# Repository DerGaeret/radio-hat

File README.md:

# Retro-Radio

Holzgehäuse mit Frontplatte und Lautsprecherabdeckungen eines DDR-Radios. Innen ein Raspberry Pi 4B mit dem **Raspberry Pi DigiAMP+** als Verstärker, sechs Tasten, drei Drehgebern (nur Drehen), dem Original-A/E-Schalter mit softem Ausschalten und, als Option, einer LED-Skala mit Senderzeiger. Alles zum Bestellen steht in **`EINKAUF.md`**.

Bis zum 17.11.2026 war hier eine eigene Verstärkerplatine (Radio HAT, TAS5805M) entworfen. Sie wird nicht gebaut; der DigiAMP+ macht dasselbe. Der letzte Stand liegt in der Git-Geschichte (Commit `c25365f`), zurückholen mit `git checkout c25365f -- KiCad JLCPCB PRUEFBERICHT.md`.

| Datei | Wofür |
|---|---|
| `Pi/asound.conf` | ALSA-Einstellung: Hochpass 50 Hz vor dem DigiAMP+ |
| `Bilder/digiamp_plus.jpg` | Lageplan des DigiAMP+ aus der Raspberry-Pi-Doku |
| `Schaltplan/` | Schaltplan (`schaltplan.pdf`, `blatt1.png`, `blatt2.png`), erzeugt mit `schaltplan.py` |
| `EINKAUF.md` | vollständige Bestellliste (Elektronik, Kleinteile, Gehäuse) |
| `Gehaeuse/` | Holzgehäuse: 3D-Modell, Maßzeichnungen, Zuschnittliste, Druckteile |

Quellen: [Produktseite](https://www.raspberrypi.com/products/digiamp-plus/), [Doku](https://www.raspberrypi.com/documentation/accessories/audio.html), [pinout.xyz](https://pinout.xyz/pinout/pi_digiamp), Overlay-Beschreibung und Treiber im Raspberry-Pi-Kernel (`overlays/README`, `sound/soc/bcm/iqaudio-dac.c`).

## DigiAMP+ in Kürze

- Verstärker TI TAS5756M (DAC und Endstufe in einem Chip, I²C-Adresse 0x4C), bis 2 × 35 W laut Produktseite. Zwei Schraubklemmen für passive Lautsprecher. Mit Blick von oben und der Netzbuchse links: links „−“, rechts „+“, an beiden Klemmen gleich.
- Versorgung 12 bis 24 V Gleichspannung, 3 A, über Hohlbuchse 5,5 × 2,5 mm (Stecker 2,5 mm innen, 5,5 mm außen, 11 mm lang). Alternativ fest verdrahtet an P5 (Polung beachten).
- Versorgt den Pi über den GPIO-Stecker mit 5,1 V, 2,5 A. **Den Pi nie zusätzlich über seinen eigenen USB-C-Anschluss versorgen.**
- Belegt GPIO2/3 (I²C), GPIO18 bis 21 (I²S), GPIO22 (Stummschaltung und Mute-LED), dazu GPIO0/1 für das HAT-EEPROM.
- 58 × 65 mm, steckt direkt auf dem Pi, Befestigung mit den mitgelieferten Abstandsbolzen auf den vier Pi-Löchern. Deren Außengewinde geht durch den Pi in die gedruckten Säulen des Pi-Halters (Bohrung Ø 2,2, M2,5 schneidet sich selbst ein); gekaufte Abstandshalter braucht es nicht. Liegen keine Bolzen bei: gedruckte Hülsen (11,5 mm) und Schrauben M2,5 × 25 von oben. Der GPIO-Stecker wird nach oben durchgeführt.
- Startet stummgeschaltet (Mute-LED leuchtet). Der Treiber schaltet beim Abspielen ein und 5 s nach dem Ende wieder stumm.
- Betrieb 0 bis 50 °C.
- Lage (Bild in der Doku, GPIO-Stecker oben): Hohlbuchse links unten an der Kante gegenüber dem GPIO-Stecker, rechts daneben die Klemmen LEFT und RIGHT, ganz links P5 (2 Pins, „−“ „+“). Diese Kante liegt über der USB-C/HDMI-Seite des Pi; die Hohlbuchse sitzt auf der Seite von Pin 1 (SD-Karten-Ende).

Bild: Raspberry Pi Ltd., Dokumentation (github.com/raspberrypi/documentation), CC BY-SA 4.0.

## Pi

Raspberry Pi 4B. Die Doku schreibt, der DigiAMP+ sei für Pi 3 und älter ausgelegt; am Pi 4 soll stromhungriges USB-Zubehör an einen USB-Hub mit eigenem Netzteil. Im Radio hängt nichts am USB des Pi: Die (optionale) LED-Skala bekommt ihre 5 V aus einem eigenen Wandler (siehe unten). Der Pi zieht am DigiAMP+ damit nur seine eigenen 0,6 bis 1,3 A von 2,5 A. Der USB-C-Anschluss des Pi bleibt immer frei. Für den Pi einen passiven Kühlkörper aufkleben, er sitzt unter dem DigiAMP+ im geschlossenen Gehäuse.

## Netzteil

Gesucht ist ein geregeltes Tischnetzteil wie bei Laptops:

| Merkmal | Wert |
|---|---|
| Spannung | **19 V** (20 V geht auch) |
| Strom | mindestens 3,42 A (65 W) |
| Stecker | Hohlstecker 5,5 × 2,5 mm, Mitte Plus |
| Art | geregeltes Schaltnetzteil, CE-Zeichen |

Gewählt (Nutzer): **Universal-Laptopnetzteil 90 W** von [Amazon](https://amzn.eu/d/09DU1uIf) (18,5–20 V, 4,74 A, Wechselstecker, Netzkabel dabei). Den Aufsteckstecker 5,5 × 2,5 mm verwenden, vor dem ersten Anschluss mit dem Multimeter prüfen, dass die Mitte Plus ist, und den Stecker mit Schrumpfschlauch gegen Abziehen sichern. Markenalternative: Mean Well GST90A19-P1M (19 V, 4,74 A; Reichelt) mit Netzkabel NKSK 200 SW. Links in `EINKAUF.md`.

- **Warum 19 V:** Die Lautsprecher (Sharp VSP0010PBS78A) haben 8 Ω und vertragen höchstens 20 W. Die Brückenendstufe schafft an 8 Ω höchstens etwa U² / 16 Ω ohne Verluste, bei 19 V also etwa 22 W, real knapp 20 W vor dem Übersteuern; bei 24 V wären es über 30 W. Das gewählte Universalnetzteil liefert 18,5–20 V; bei 20 V sind es real etwa 22 W. Deshalb in der Software die Lautstärke auf etwa −1 dB begrenzen (ALSA „Digital“ höchstens etwa 205 statt 207), dann bleiben die Lautsprecher unter 20 W.
- **Leistung:** Verstärker bei Dauer-Sinus voll aufgedreht bis etwa 45 W, Pi über den DigiAMP+ bis etwa 15 W, LED-Skala (optional) bis 5 W (auf 0,8 A begrenzt, siehe unten). Mit Musik liegt der Mittelwert weit darunter; 65 W reichen.

## Stromversorgung und A/E-Schalter (softes Ausschalten)

Das Netzteil wird hinten am Radio eingesteckt. Der Original-A/E-Schalter (RFT) mit dem Originalknopf bleibt erhalten, schaltet aber nur noch ein Steuersignal von etwa 0,4 mA. Die 19 V schaltet ein fertiges Modul, der **Pololu Big MOSFET Slide Switch MP** (#2814, 4,5–32 V, 4 A Dauerstrom bei 55 °C, Verpolungsschutz, bei Eckstein 6,53 €). Damit ist es egal, wie viel Strom der alte Schalter verträgt.

Welche Variante: Pololu baut das Modul in vier Ausführungen. Mini LV verträgt nur 20 V (zu knapp an 19 V), Mini SV nur 2 A Dauerstrom. MP (4 A) und HP (6 A) haben dieselbe Schaltung, nur andere MOSFETs. Das Radio zieht mit Musik meist unter 1,5 A aus den 19 V; nur bei Dauer-Sinus voll aufgedreht etwa 3,2 A (mit LEDs 3,5 A). Dafür reicht MP. HP wäre nur Reserve und ist bei Eckstein nicht gelistet.

```
Einbaubuchse hinten ──► Pololu MP: VIN      VOUT ──┬──► DC-Kabel mit Hohlstecker ──► DigiAMP+ (19 V) ──► Pi (5,1 V)
                                                     └──► (optional) Pololu D24V10F5 (5 V, 1 A) ──► LED-Skala
                         SW ◄─ BAT85 ─┐
                                      X ── A/E-Schalter ── GND
              Pi GPIO10 ── BAT85 ────┘
              Pi GPIO9  ──────────────► ON
```

So funktioniert es:

- **Einschalten:** A/E zu → X und damit SW auf Masse → das Modul schaltet die 19 V durch → DigiAMP+ und Pi starten. Beim Booten setzt der Pi GPIO9 auf high (Eingang ON des Moduls) und hält sich damit selbst.
- **Ausschalten:** A/E auf → GPIO10 geht über seinen Pull-up auf high → der Pi fährt sauber herunter (`gpio-shutdown`) → ganz am Ende zieht er GPIO9 auf low (`gpio-poweroff`) → das Modul schaltet ab. Dauer etwa 10 bis 20 s; die grüne LED am Modul geht dann aus.
- Die beiden Schottky-Dioden BAT85 trennen die Wege: Solange der Pi über ON selbst hält, sieht GPIO10 trotzdem, ob der Schalter offen ist. Ist der Pi aus, liegen an X etwa 19 V; die Diode zu GPIO10 sperrt dann (BAT85: 30 V).
- **Neustart** (`sudo reboot`) bei geschlossenem Schalter geht normal. `sudo poweroff` bei geschlossenem Schalter hält den Pi nur an, der Strom bleibt an; dann A/E aus- und wieder einschalten. Im Alltag nur mit A/E ausschalten.
- Hängt der Pi einmal, bleibt der Strom an, auch wenn A/E aus ist. Dann den Netzstecker ziehen.
- Ohne Strom vom Netzteil verbraucht das Modul im Aus weniger als 0,2 µA; was im Aus bleibt, ist der Leerlauf des Netzteils.

### Steuerplatine (Lochraster 70 × 50 mm)

Schaltplan: `Schaltplan/schaltplan.pdf` (Blatt 1).

Sitzt im Technikfach rechts neben dem Pi auf dem Druckteil `steuer_halter`. Bauteile und Verbindungen:

| Teil | Anschluss | Verbindung |
|---|---|---|
| Schraubklemme EIN (2-polig, RM 5,08) | + / − | Einbaubuchse hinten (Delock 90188, 9 A, Mittelstift +), 0,75 mm² |
| Pololu Big MOSFET Slide Switch MP | VIN, GND | Klemme EIN |
| | VOUT, GND | Klemme VERST (zum DigiAMP+) und, falls Beleuchtung, VIN des 5-V-Wandlers |
| | SW | Anode der ersten BAT85; Kathode an Punkt X |
| | ON | Pi GPIO9 (Pin 21) |
| | Schiebeschalter auf dem Modul | auf **OFF** stellen, sonst bleibt alles immer an |
| Schraubklemme A/E (2-polig) | X / GND | Original-A/E-Schalter, beliebige Litze |
| zweite BAT85 | Anode Pi GPIO10 (Pin 19), Kathode X | |
| Schraubklemme VERST (2-polig) | + / − | selbst gelötetes Kabel: Silikonlitze 0,75 mm² mit Hohlstecker 5,5 × 2,5 (Lumberg 1634 02) zum DigiAMP+, Mitte + |
| *optional:* Pololu D24V10F5 | VIN, GND, VOUT | VIN an VOUT des Schaltmoduls; VOUT = 5 V für die LEDs. PG frei lassen |
| *optional:* Elko 1000 µF / 10 V | 5 V gegen GND | direkt am 5-V-Ausgang |
| *optional:* 74HCT245 (DIP-20, im Sockel) | 20 = 5 V, 10 = GND, 1 (DIR) = 5 V, 19 (/OE) = GND, 2 (A1) = Pi GPIO12 (Pin 32), 18 (B1) → 330 Ω → LED-Daten | Pins 3–9 an GND, 11–17 frei; 100 nF zwischen 20 und 10 |
| *optional:* Schraubklemme LED (3-polig) | 5 V / Daten / GND | zum Lichtkasten, 3 Adern 0,5 mm² |
| Stiftleiste 1 × 4 | GPIO9, GPIO10, GPIO12 (nur mit Beleuchtung), GND | Dupont-Kabel zum durchgeführten GPIO-Stecker des DigiAMP+ |

Der 74HCT245 hebt das 3,3-V-Datensignal des Pi auf 5-V-Pegel: Er erkennt ab 2,0 V „high“ und gibt volle 5 V aus; WS2812B verlangen mindestens 0,7 × 5 V = 3,5 V. Von den acht Kanälen wird nur einer gebraucht.

### LED-Skala (optional): Aufbau, Strom und Wärme

Die Beleuchtung ist ein Zusatz. Ohne sie fallen weg: Lichtkasten (Druckteil), LED-Streifen, 5-V-Wandler, 74HCT245 mit Sockel, 330 Ω, 100 nF, beide 1000-µF-Elkos, die 3-polige Klemme und die Leitung an GPIO12. Alles andere bleibt gleich; nachrüsten geht jederzeit, wenn auf der Steuerplatine Platz dafür gelassen wird.

- 4 Streifen WS2812B (144 LEDs/m) à 28 LEDs = 112 LEDs, je einer hinter den Schlitzen U, K, L und hinter den Stationsmarken. Daten in Reihe (Ende eines Streifens an den Anfang des nächsten), 5 V und GND an jedem Streifen einzeln vom Klemmenpunkt im Lichtkasten. Am Lichtkasten ein zweiter Elko 1000 µF / 10 V.
- **So leuchten die Sender:** Auf der Frontplatte sind die Stationsmarken kleine durchsichtige Felder (etwa 10 × 3 mm) in zwei Reihen neben den Sendernamen (R. Wolga, Radio DDR, Poznan, Moskva, Stimme d. DDR, Budapest …). Hinter beiden Reihen liegt ein gemeinsamer LED-Streifen in einer eigenen Kammer; der weiße Diffusor verteilt das Licht. Im Grundzustand leuchten alle Marken gleichmäßig wie früher mit der Skalenlampe. Der Senderzeiger ist eine rote LED-Spalte, die in allen vier Reihen an derselben Stelle leuchtet. Weil eine Marke 10 mm breit ist und die LEDs 6,9 mm Abstand haben, liegen hinter jeder Marke ein bis zwei eigene LEDs. Die Software kann also zusätzlich die Marke des eingestellten Senders heller oder in einer anderen Farbe leuchten lassen. Dazu muss nur die Lage jeder Marke (in mm ab linker Plattenkante) einmal ausgemessen werden. Eine Marke der oberen und eine der unteren Reihe an derselben Stelle leuchten immer zusammen.
- **Strom:** Jede LED zieht bei vollem Weiß bis 60 mA, alle zusammen 6,7 A; dazu etwa 1 mA je LED in Ruhe (0,11 A). Der Pololu D24V10F5 liefert 1 A. **In der Software auf 0,8 A begrenzen**: Weiß höchstens 10 %, Warmweiß bis etwa 15 %. Als Skalenlicht reicht das. Wer heller will, nimmt den D36V28F5 (3,2 A, bei Eckstein 26,12 €) und begrenzt auf 2 A.
- **Wärme:** 4 W im PLA-Lichtkasten sind unkritisch.
- Früher geplant war ein RP2040-Zero am USB des Pi. Das hätte bis zu 1,2 A zusätzlich über den 5-V-Regler des DigiAMP+ gezogen, der für Pi und USB zusammen nur 2,5 A hat. Jetzt kommt der Strom aus dem eigenen Wandler, und die Daten kommen direkt vom Pi (PWM an GPIO12, Bibliothek `rpi_ws281x`).

## Anschlüsse an den Pi

Alles kommt mit Dupont-Kabeln (Buchse) an den durchgeführten GPIO-Stecker oben auf dem DigiAMP+. Tasten und Drehgeber schalten gegen GND.

| Bauteil | GPIO | Pin |
|---|---|---|
| Taste 1 | GPIO17 | 11 |
| Taste 2 | GPIO27 | 13 |
| Taste 3 | GPIO4 | 7 |
| Taste 4 | GPIO23 | 16 |
| Taste 5 | GPIO24 | 18 |
| Taste 6 | GPIO25 | 22 |
| Drehgeber Klang (A, B) | GPIO5, GPIO6 | 29, 31 |
| Drehgeber Lautstärke (A, B) | GPIO13, GPIO16 | 33, 36 |
| Drehgeber Sender (A, B) | GPIO11, GPIO8 | 23, 24 |
| A/E-Schalter lesen (über BAT85) | GPIO10 | 19 |
| Selbsthaltung (ON des Schaltmoduls) | GPIO9 | 21 |
| LED-Daten (über 74HCT245, optional) | GPIO12 | 32 |
| 3,3 V für die Pull-ups der Drehgeber | – | 1 oder 17 |
| GND | – | 6, 9, 14, 20, 25, 30, 34, 39 |

Vom DigiAMP+ belegt: GPIO0/1, 2/3, 18 bis 21, 22. Frei bleiben GPIO7, 14, 15 und 26 (Pins 26, 8, 10, 37). Geändert gegenüber dem Entwurf mit eigener Platine: Taste 3 von GPIO22 auf GPIO4; Drehgeber ohne Taster.

- **Tasten (Cherry MX Blue):** Pull-ups im Pi, in der Software einschalten, 20 ms entprellen.
- **Drehgeber (ALPS STEC12E07, 24 Rastungen, 24 Impulse, ohne Taster):** 12-mm-Bauform zum Einschnappen in die Platine, Welle Ø 6 abgeflacht (laut Reichelt 10 mm lang). Pins A, C, B im Raster 2,5 mm passen ins Lochraster; für die zwei Haltelaschen die Löcher auf Ø 2 aufbohren. Belastbarkeit laut Datenblatt 0,5 mA bei 5 V. Die Pull-ups im Pi (etwa 50 kΩ, 0,07 mA) sind für Dauerbetrieb knapp; deshalb auf jede Lochrasterplatine zwei Widerstände: 10 kΩ von A nach 3,3 V und 10 kΩ von B nach 3,3 V (je 0,33 mA). Pin C (Mitte) an GND. Pro Drehgeber ein Kabel mit 4 Adern: A, B, 3,3 V, GND.

```
          Drehgeber, Pins von hinten:   A    C    B
                                        │    │    │
   Pi GPIO (A) ◄────────────────────────┤    │    ├────────────────────────► Pi GPIO (B)
                                      10 kΩ  │  10 kΩ
                                        │    │    │
   Pi 3,3 V (Pin 1/17) ─────────────────┴────┼────┘
   Pi GND ───────────────────────────────────┘
```

## Pi einrichten

Den DigiAMP+ (grüne Ausführung) aufstecken und verschrauben, Lautsprecher anklemmen, Strom ein. Der Pi startet mit.

Erkennung prüfen:

```bash
grep -a . /proc/device-tree/hat/*
```

Dort muss „Raspberry Pi Ltd.“ stehen. Das HAT-EEPROM lädt den Treiber dann von selbst. Nur wenn nichts erkannt wird, in `/boot/firmware/config.txt` eintragen:

```
dtoverlay=
dtoverlay=rpi-digiampplus
```

Außerdem in `/boot/firmware/config.txt`:

```
dtparam=audio=off
dtoverlay=gpio-shutdown,gpio_pin=10,active_low=0,gpio_pull=up,debounce=200
dtoverlay=gpio-poweroff,gpiopin=9,active_low=1
dtoverlay=rotary-encoder,pin_a=5,pin_b=6,relative_axis=1,steps-per-period=4
dtoverlay=rotary-encoder,pin_a=13,pin_b=16,relative_axis=1,steps-per-period=4
dtoverlay=rotary-encoder,pin_a=11,pin_b=8,relative_axis=1,steps-per-period=4
```

und die vorhandene Zeile `dtoverlay=vc4-kms-v3d` zu `dtoverlay=vc4-kms-v3d,noaudio` ändern. Dann ist der DigiAMP+ die einzige Soundkarte (Karte 0).

- `24db_digital_gain` **nicht** setzen. Ohne diesen Schalter lässt der Treiber die Lautstärke („Digital“) höchstens bis 0 dB zu; darüber würde laute Musik übersteuert.
- SPI ausgeschaltet lassen (`dtparam=spi=on` darf nicht aktiv sein), weil GPIO8 und 11 für den Drehgeber Sender gebraucht werden.
- `gpio-shutdown` an GPIO10: Öffnen des A/E-Schalters (GPIO10 wird high) fährt den Pi herunter. `gpio-poweroff` an GPIO9 mit `active_low`: GPIO9 ist im Betrieb high und geht am Ende des Herunterfahrens (und bei jedem Neustart kurz) auf low; dann schaltet das Pololu-Modul ab, sofern A/E offen ist.
- Die alten Einträge der eigenen Platine (`hifiberry-dac`, `gpio-poweroff,gpiopin=4`) dürfen nicht mehr drinstehen; GPIO4 ist jetzt Taste 3.
- Beim STEC12E07 ergibt jede Rastung einen vollen Impulszyklus, daher `steps-per-period=4`. Stimmt die Drehrichtung nicht, A und B tauschen.

Neu starten und prüfen:

```bash
aplay -l
```

zeigt Karte 0 „RPi DigiAMP+“.

Hochpass einrichten (optional, empfohlen für die kleinen Lautsprecher):

```bash
sudo apt install libasound2-plugins swh-plugins alsa-utils
```

```bash
sudo install -m 644 Pi/asound.conf /etc/asound.conf
```

Grundlautstärke setzen und speichern:

```bash
amixer -c 0 sset Digital -- -24dB
```

```bash
sudo alsactl store
```

Eigene Programme stellen die Lautstärke über das ALSA-Element „Digital“ ein (in MPD: `mixer_type "hardware"`, `mixer_control "Digital"`).

LED-Skala (falls eingebaut): Bibliothek `rpi_ws281x` (Python: `sudo pip3 install rpi_ws281x --break-system-packages`), PWM-Kanal 0 an GPIO12, 112 LEDs, Typ GRB, Programm als root. Helligkeit im Programm fest begrenzen (siehe „LED-Skala: Strom und Wärme“). Die PWM ist frei, weil der analoge Audioausgang mit `dtparam=audio=off` aus ist.

## Erster Test

1. Steuerplatine ohne Pi, DigiAMP+ und LEDs: Netzteil hinten einstecken. A/E aus: grüne LED am Modul aus, 0 V an VERST. A/E ein: LED an, am Hohlstecker des Kabels zum DigiAMP+ innen +19 bis +20 V, außen Minus; am 5-V-Ausgang (falls Beleuchtung) 4,8 bis 5,2 V.
2. Lautsprecher abklemmen, DigiAMP+ auf den Pi, Hohlstecker und Dupont-Kabel (GPIO9, 10, 12, GND) stecken, A/E ein. Power-LED am DigiAMP+ an, Mute-LED an.
3. Pi bootet. `aplay -l` zeigt „RPi DigiAMP+“.
4. Lautsprecher anklemmen. `speaker-test -c 2 -t wav` spielt abwechselnd links und rechts; die Mute-LED geht beim Abspielen aus.
5. Hochpass prüfen: `speaker-test -c 2 -t sine -f 30` muss deutlich leiser sein als `-f 100`.
6. Ohne Musik das Ohr an den Lautsprecher halten: kein Brummen oder Zirpen.
7. A/E aus: Der Pi fährt herunter, nach 10 bis 20 s geht die grüne LED am Modul aus. A/E wieder ein: Der Pi startet.
8. Falls Beleuchtung: LED-Skala zuerst mit 5 % Helligkeit testen, Strom am 5-V-Ausgang messen (höchstens 0,8 A).

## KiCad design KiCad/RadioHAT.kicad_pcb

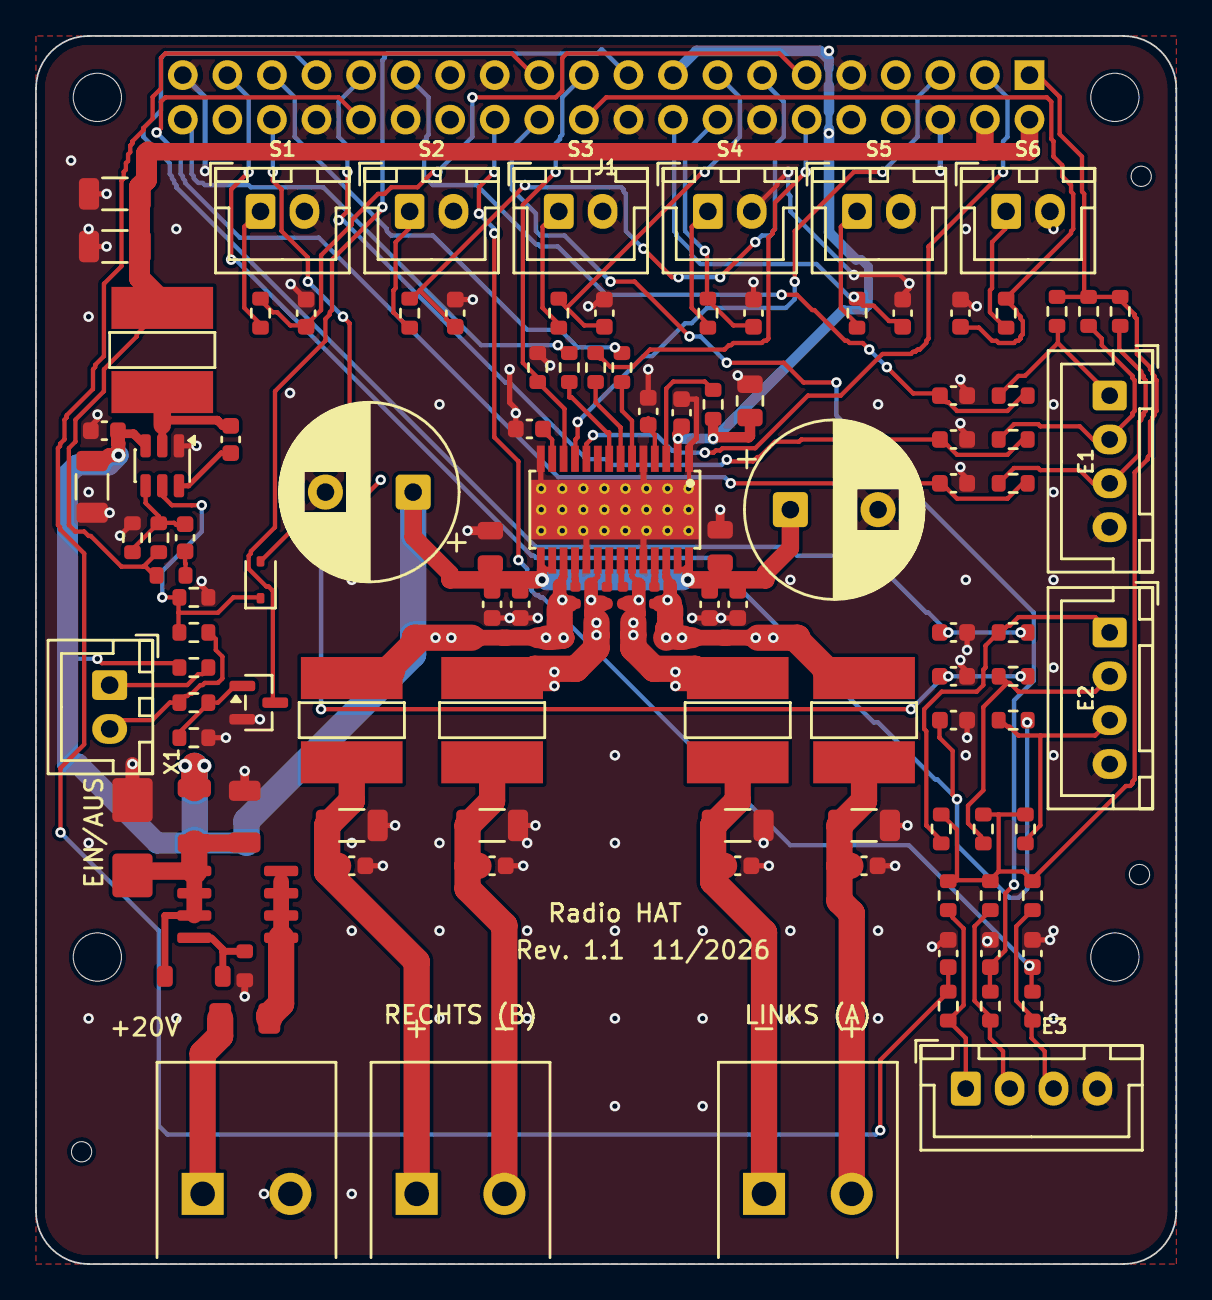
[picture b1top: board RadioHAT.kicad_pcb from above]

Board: 4 copper layers, 65.0 x 70.0 mm, 119 parts (0 on the bottom side), 73 nets.

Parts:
C1, C2: 470uF 35V; CP_Radial_D10.0mm_P5.00mm
C3, C5, C9, C10: 1uF 50V X5R; C_0603_1608Metric
C4, C6, C8, C24, C25, C37, C38, C39, C40, C41, C42, C43, C44, C45: 100nF 50V X7R; C_0603_1608Metric
C7: 4.7uF 25V X5R; C_0805_2012Metric
C11, C12, C13, C14: 220nF 16V X7R; C_0402_1005Metric
C15, C16, C17, C18: 680nF 50V X7R; C_1206_3216Metric
C19, C20, C21, C22: 1nF 50V X7R; C_0603_1608Metric
C23, C46: 10uF 50V X5R; C_1206_3216Metric
C26, C27: 22uF 25V X5R; C_1206_3216Metric
C28: 100pF 50V C0G; C_0603_1608Metric
C31, C32, C33, C34, C35, C36: 10nF 50V X7R; C_0603_1608Metric
C47, C48: 10uF 50V X5R; C_0805_2012Metric
D1: 1N5819WS; D_SOD-323
D2: SMBJ22A; D_SMB
D3: BZT52C15; D_SOD-123
E1: Encoder 1; JST_XH_B4B-XH-A_1x04_P2.50mm_Vertical
E2: Encoder 2; JST_XH_B4B-XH-A_1x04_P2.50mm_Vertical
E3: Encoder 3; JST_XH_B4B-XH-A_1x04_P2.50mm_Vertical
F1: 5A T 63V; Fuse_1206_3216Metric
FB1: BLM31KN121SN1L; L_1206_3216Metric
H1, H2, H3, H4: M2.5; MountingHole_2.75mm_M2.5
J1: Buchsenleiste 2x20 (Unterseite); PinSocket_2x20_P2.54mm_Vertical
J2: Lautsprecher rechts; TerminalBlock_1x02_P5.00mm
J3: Lautsprecher links; TerminalBlock_1x02_P5.00mm
J4: Netzteil 20V; TerminalBlock_1x02_P5.00mm
L1, L2, L3, L4, L5: 10uH 3.5A; L_6045
Q1: MMBT3904; SOT-23
Q2: AO4407A; SOIC-8_3.9x4.9mm_P1.27mm
R1: 15k 1%; R_0603_1608Metric
R2, R7, R10, R13: 10k 1%; R_0603_1608Metric
R3, R4, R5: 33R 1%; R_0603_1608Metric
R6: 75k 1%; R_0603_1608Metric
R8, R11, R12: 100k 1%; R_0603_1608Metric
R9: 470k 1%; R_0603_1608Metric
R14: 2k 1%; R_0603_1608Metric
R21, R22, R23, R24, R25, R26, R27, R28, R29, R30, R31, R32, R33, R34, R35: 1k 1%; R_0603_1608Metric
R41, R42, R44, R45, R47, R48: 2.7k 1%; R_0603_1608Metric
R43, R46, R49: 270R 1%; R_0603_1608Metric
S1: Taste 1; JST_XH_B2B-XH-A_1x02_P2.50mm_Vertical
S2: Taste 2; JST_XH_B2B-XH-A_1x02_P2.50mm_Vertical
S3: Taste 3; JST_XH_B2B-XH-A_1x02_P2.50mm_Vertical
S4: Taste 4; JST_XH_B2B-XH-A_1x02_P2.50mm_Vertical
S5: Taste 5; JST_XH_B2B-XH-A_1x02_P2.50mm_Vertical
S6: Taste 6; JST_XH_B2B-XH-A_1x02_P2.50mm_Vertical
TH1, TH2, TH3: Passbohrung 1,152 mm; Passbohrung_JLCPCB_1.152mm
U1: TAS5805MPWPR; TAS5805M_PWP28
U2: TPS54308DDCR; TSOT-23-6
X1: Ein/Aus; JST_XH_B2B-XH-A_1x02_P2.50mm_Vertical

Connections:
+3V3: C7.1, C8.1, J1.17, R1.1, U1.2
+5V: C26.1, C27.1, J1.2, J1.4, L5.2, R6.1, R14.1
ADR: R1.2, U1.3
AVDD: C9.1, U1.13
BOOT: C25.1, U2.6
BSTA+: C14.1, U1.25
BSTA-: C13.1, U1.22
BSTB+: C11.1, U1.18
BSTB-: C12.1, U1.21
EN: D1.1, R8.1, R9.1, U2.5
FB: C28.2, R6.2, R7.1, U2.4
FB_FF: C28.1, R14.2
GND: C1.2, C2.2, C3.2, C4.2, C5.2, C6.2, C7.2, C8.2, C9.2, C10.2, C15.2, C16.2, C17.2, C18.2, C19.2, C20.2, C21.2, C22.2, C23.2, C24.2, C26.2, C27.2, C31.2, C32.2, C33.2, C34.2, C35.2, C36.2, C37.2, C38.2, C39.2, C40.2, C41.2, C42.2, C43.2, C44.2, C45.2, C46.2, C47.2, C48.2, D2.2, E1.4, E2.4, E3.4, J1.6, J1.9, J1.14, J1.20, J1.25, J1.30, J1.34, J1.39, J4.2, Q1.2, R2.2, R7.2, R8.2, R12.2, R13.1, S1.2, S2.2, S3.2, S4.2, S5.2, S6.2, U1.1, U1.5, U1.14, U1.19, U1.24, U1.29, U2.1
GPIO5: C37.1, J1.29, R27.2
GPIO6: C38.1, J1.31, R28.2
GPIO7: C45.1, J1.26, R35.2
GPIO8: C44.1, J1.24, R34.2
GPIO11: C43.1, J1.23, R33.2
GPIO12: C39.1, J1.32, R29.2
GPIO13: C40.1, J1.33, R30.2
GPIO16: C41.1, J1.36, R31.2
GPIO17: C31.1, J1.11, R21.2
GPIO22: C33.1, J1.15, R23.2
GPIO23: C34.1, J1.16, R24.2
GPIO24: C35.1, J1.18, R25.2
GPIO25: C36.1, J1.22, R26.2
GPIO26: C42.1, J1.37, R32.2
GPIO27: C32.1, J1.13, R22.2
HOLD: D1.2, J1.7
IN5_C: E1.1, R27.1, R41.1
IN6_C: E1.2, R28.1, R42.1
IN7_C: E3.3, R35.1, R49.1
IN8_C: E3.2, R34.1, R48.1
IN11_C: E3.1, R33.1, R47.1
IN12_C: E1.3, R29.1, R43.1
IN13_C: E2.1, R30.1, R44.1
IN16_C: E2.2, R31.1, R45.1
IN17_C: R21.1, S1.1
IN22_C: R23.1, S3.1
IN23_C: R24.1, S4.1
IN24_C: R25.1, S5.1
IN25_C: R26.1, S6.1
IN26_C: E2.3, R32.1, R46.1
IN27_C: R22.1, S2.1
LRCLK: R3.2, U1.6
LRCLK_PI: J1.35, R3.1
OUTA+: C14.2, L4.1, U1.26
OUTA-: C13.2, L3.1, U1.23
OUTB+: C11.2, L1.1, U1.17
OUTB-: C12.2, L2.1, U1.20
PDN: J1.21, R2.1, U1.12
PVDD: C1.1, C2.1, C3.1, C4.1, C5.1, C6.1, C23.1, C24.1, C47.1, C48.1, FB1.2, R10.1, U1.15, U1.16, U1.27, U1.28, U2.3
PWR_SENSE: J1.19, Q1.3
Q1B: Q1.1, R11.2, R12.1
Q2G: D3.2, Q2.4, R13.2
SCL: J1.5, U1.11
SCLK: R4.2, U1.7
SCLK_PI: J1.12, R4.1
SDA: J1.3, U1.10
SDIN: R5.2, U1.8
SDIN_PI: J1.40, R5.1
SPKA+: C18.1, C22.1, J3.2, L4.2
SPKA-: C17.1, C21.1, J3.1, L3.2
SPKB+: C15.1, C19.1, J2.1, L1.2
SPKB-: C16.1, C20.1, J2.2, L2.2
SW: C25.2, L5.1, U2.2
SW_FEED: R10.2, X1.1
SW_ON: R9.2, R11.1, X1.2
VENC: J1.1, R41.2, R42.2, R43.2, R44.2, R45.2, R46.2, R47.2, R48.2, R49.2
VIN: F1.1, J4.1
VIN_F: F1.2, Q2.5, Q2.6, Q2.7, Q2.8
VIN_P: C46.1, D2.1, D3.1, FB1.1, Q2.1, Q2.2, Q2.3
VR_DIG: C10.1, U1.4

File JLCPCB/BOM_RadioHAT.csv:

Comment,Designator,Footprint,LCSC Part #
TAS5805MPWPR,U1,TAS5805M_PWP28,C478472
1uF 50V X5R,"C3,C5,C9,C10",C_0603_1608Metric,C15849
100nF 50V X7R,"C4,C6,C8,C24,C25,C37,C38,C39,C40,C41,C42,C43,C44,C45",C_0603_1608Metric,C14663
4.7uF 25V X5R,C7,C_0805_2012Metric,C1779
220nF 16V X7R,"C11,C12,C13,C14",C_0402_1005Metric,C16772
10uH 3.5A,"L1,L2,L3,L4,L5",L_6045,C79272
680nF 50V X7R,"C15,C16,C17,C18",C_1206_3216Metric,C1881
1nF 50V X7R,"C19,C20,C21,C22",C_0603_1608Metric,C1588
15k 1%,R1,R_0603_1608Metric,C22809
10k 1%,"R2,R7,R10,R13",R_0603_1608Metric,C25804
33R 1%,"R3,R4,R5",R_0603_1608Metric,C23140
TPS54308DDCR,U2,TSOT-23-6,C168839
10uF 50V X5R,"C23,C46",C_1206_3216Metric,C13585
22uF 25V X5R,"C26,C27",C_1206_3216Metric,C12891
75k 1%,R6,R_0603_1608Metric,C23242
100pF 50V C0G,C28,C_0603_1608Metric,C14858
100k 1%,"R8,R11,R12",R_0603_1608Metric,C25803
470k 1%,R9,R_0603_1608Metric,C23178
1N5819WS,D1,D_SOD-323,C191023
MMBT3904,Q1,SOT-23,C20526
1k 1%,"R21,R22,R23,R24,R25,R26,R27,R28,R29,R30,R31,R32,R33,R34,R35",R_0603_1608Metric,C21190
10nF 50V X7R,"C31,C32,C33,C34,C35,C36",C_0603_1608Metric,C57112
2.7k 1%,"R41,R42,R44,R45,R47,R48",R_0603_1608Metric,C13167
270R 1%,"R43,R46,R49",R_0603_1608Metric,C22966
AO4407A,Q2,SOIC-8_3.9x4.9mm_P1.27mm,C16072
5A 63V 1206 Slow-Blow,F1,Fuse_1206_3216Metric,C553937
SMBJ22A,D2,D_SMB,C10214
BZT52C15,D3,D_SOD-123,C2104
BLM31KN121SN1L,FB1,L_1206_3216Metric,C337884
10uF 50V X5R 0805,"C47,C48",C_0805_2012Metric,C2932476
2k 1%,R14,R_0603_1608Metric,C22975

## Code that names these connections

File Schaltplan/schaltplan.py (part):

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    u2 = ic(d, (25, -9), '*U2 74HCT245 (DIP-20)\n(nur mit Beleuchtung)',
            links=[('A1 (2)', 'A'), ('DIR (1)', 'DIR'), ('/OE (19)', 'OE'), ('GND (10)', 'G')],
            rechts=[('B1 (18)', 'Y'), ('VCC (20)', 'V')], w=4)
    tag(d, u2.A, 'GPIO12 (Pin 32)', 'left', 1.0)
    tag(d, u2.DIR, '+5V_LED', 'left', 1.0)
    d.add(elm.Line().at(u2.OE).left().length(0.6)); d.add(elm.Ground())
    d.add(elm.Line().at(u2.G).left().length(0.6)); d.add(elm.Ground())
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    titel(d, (0, 13), 'Blatt 2: Raspberry Pi 4B, Tasten, Drehgeber',
          'Alle Verbindungen mit Dupont-Kabeln am durchgeführten GPIO-Stecker oben auf dem DigiAMP+. Pull-ups der Tasten im Pi (Software).')
    pins = [  # (Pin, Name)
        ('1', '3V3'), ('7', 'GPIO4'), ('9', 'GND'), ('11', 'GPIO17'), ('13', 'GPIO27'),
        ('16', 'GPIO23'), ('17', '3V3'), ('18', 'GPIO24'), ('19', 'GPIO10'), ('21', 'GPIO9'),
        ('22', 'GPIO25'), ('23', 'GPIO11'), ('24', 'GPIO8'), ('29', 'GPIO5'), ('31', 'GPIO6'), ('32', 'GPIO12'),
        ('33', 'GPIO13'), ('36', 'GPIO16'), ('39', 'GND')]
    links = [(f'{n} ({p})', f'P{p}') for p, n in pins[:10]]
    rechts = [(f'{n} ({p})', f'P{p}') for p, n in pins[10:]]
    pi = ic(d, (10, 4), 'Raspberry Pi 4B, 40-pol. GPIO\n(über DigiAMP+ durchgeführt)\nDigiAMP+ belegt GPIO0–3, 18–22',
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    d.add(elm.Line().at(pi.P22).right().length(1.5))
    d.add(elm.Button().right().label('S6 Cherry MX', fontsize=7)); d.add(elm.Ground().theta(0))
    tag(d, pi.P21, 'GPIO9 → Blatt 1 (ON)', 'left', 0.8)
    tag(d, pi.P32, 'GPIO12 → Blatt 1 (LED, optional)', 'right', 0.8)
    d.add(elm.Line().at(pi.P39).right().length(0.8)); d.add(elm.Ground())
    for p, n in (('29', 'E1_A'), ('31', 'E1_B'), ('33', 'E2_A'), ('36', 'E2_B'),
                 ('23', 'E3_A'), ('24', 'E3_B')):
        tag(d, getattr(pi, 'P' + p), n, 'right', 0.8)
    d.add(elm.Label().at((0, -2.6)).label('Tasten S1–S6: Reihenfolge von links nach rechts in der Frontplatte (L, M, K, U, TA-TB, AFC-AUS). '
                                         'Frei: GPIO7, 14, 15, 26.', fontsize=7, halign='left'))

    # Drehgeber ohne Taster. Pins von vorne gesehen A, C, B nebeneinander.
    for i, (n, name) in enumerate((('E1', 'Klang'), ('E2', 'Lautstärke'), ('E3', 'Sender'))):
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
